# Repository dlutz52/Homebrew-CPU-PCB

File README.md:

# Homebrew CPU Project PCB

My inspiration for this PCB came from following Ian Ward's project on his web site:

[20xt6 Homebrew CPU Project](https://excess.org/cpu/)

This PCB implements the [LCD Character Display: Milestone 1 Complete!](https://www.youtube.com/watch?v=neW9uogt1gw) stage of this series of videos. 

But there is more to come in the future, so checkout Ian's videos on his future plans:

[Discrete Logic Rhythm Game Prototype (no CPU)](https://www.youtube.com/watch?v=yo5xX4GLc_U)

[Designing a Rhythm Game: Homebrew CPU Plan Step 2](https://www.youtube.com/watch?v=taPa7SQpib4)

[Maze Game Prototype (no CPU!)](https://www.youtube.com/shorts/fGyHHWiAYDM)

I will try to keep up with him.

PCB Front Image

PCB Back Image

# Homebrew CPU PCB BOM

## Wed, Mar 21, 2024, 08:58:15

## Component Count: 25

Ref | Qty | Value | Vendor\Part # | Description
----|-----|-------|---------------|-----------
C1, C3, C5 | 3 | 10uF | Generic | Electrolytic capacitor
C2, C4, C6 | 2 | .01uF | Digikey\FG28C0G1H103JNT06 | Unpolarized capacitor 
D1 | 1 | YELLOW\Reset | Generic | LED\3mm\Yellow
D2 | 1 | RED\HALT | Generic | LED\3mm\Red 
D3 | 1 | BLUE\CLOCK | Generic | LED\3mm\Blue
D4, D5 | 2 | 10_SEG_LED BAR_GRAPH (Blue) | Digikey\1497-1079-5-ND | LED Bar Graph\Blue\1x10 
D6 | 1 | 10_SEG_LED  BAR_GRAPH (Yellow) | Digikey\754-1179-5-ND | LED Bar Graph\Yellow\1x10 
D7 | 1 | GREEN | Generic | LED\3mm\Green 
J1 | 1 | PinSocket_1x16_P2.54mm_Vertical | Generic | Female Pin Header\1x16\2.54mm pitch
J2 | 1 | UJC-HP-M-G-5-MSMT-TR | Digikey\2223-UJC-HP-M-G-5-MSMT-TRDKR-ND | Type C/20 VDC/3A/Horizontal/6 Pin/Power Only
R1, R3, R8 | 3 | 1Kohm | Digikey\13-MFR-25FTE52-1KCT-ND | Resistor\1Kohm\1%\1/4W\Axial
R2, R6, R7, R9 | 4 | 330ohm | Digikey\13-MFR-25FRF52-330RCT-ND | Resistor\330ohm\1%\1/4W\Axial
R4 | 1 | 220ohm | Generic | Resistor\220ohm\1%\1/4W\Axial
R5 | 1 | 3ohm | Generic | Resistor\3ohm\1%\1/4W\Axial
R10, R11 | 2 | 5.1Kohm | Digikey\13-MFR-25FTE52-5K1CT-ND | Resistor\5K1ohm\1%\1/4W\Axial
RN1, RN2, RN3 | 3 | 470ohm | Digikey\4609X-101-471LF-ND | Resistor Array\8 Resistors\470ohm\9SIP
RV1 | 1 | 10Kohm | Jameco\2276439 | Panasonic EWAQ30C15A14 Audio Slide Pot
RV2, RV3 | 2 | 5Kohm | Digikey\3386P-1-502LF | Trimmer Pot\5Kohms\0.5W\1/2W\Through Hole
SW1 | 1 | TL2230 | Digikey\EG6031-ND | Switch\Pushbutton\DPDT\Through Hole
S1 | 1 | REG SELECT | Digikey\450-1654-ND | Switch\Tactile\SPST-NO\0.05A\24V\Through Hole
S2 | 1 | ENABLE | Digikey\450-1654-ND | Switch\Tactile\SPST-NO\0.05A\24V\Through Hole
U1, U3 | 2 | LM555 | Digikey\LM555CNNS/NOPB-ND | 555 Timer/Oscillator\100kHz\8-PDIP
U2 | 1 | 74LS00 | Digikey\296-1626-ND | NAND Gate IC 4 Channel 14-PDIP
U4, U5, U6, U7, U8 | 5 | 74LS163 | Digikey\296-3661-5-ND | Binary Counter\4 Bit\Positive Edge\16-PDIP
U9, U10 | 2 | SST39SF040-70-4C-PHE | Digikey\SST39SF040-70-4C-PHE-ND | FLASH Memory\4Mbit\70ns\32-PDIP

The LCD and its 16-pin male header are represented only with 3D models, but you need a 2004 LCD with a soldered 16-pin male header with a pitch of 2.54mm to plug into the 16 pin female header to complete this PCB. I have found the best place to get these is on eBay.

Do NOT try to use a 2004 LCD with an I<sup>2</sup>C adapter on it.

Most symbols/footprints/models are contained under the 'libraries' directory. Capacitors, resistors and LEDs use KiCad symbols/footprints/models.

KiCad 7.0.10 was used to create this PCB. KiCad 8.0.1 is out now and this project opens in that version. The newer KiCad will warn that this project was created in previous version and will be saved in a the newer format. When closing the schematic or a PCB just discard any changes. If you do not you will not be able to use KiCad 7 any more without difficulties.

Models in KiCad's 3D view will display an appropriate socket under the ICs but these can be omitted on the PCB - they are used to make it easier to replace any components should they need it in the future. The only exceptions are the sockets for the SST39SF040 FLASH chips. These chips can be changed out for different program\lookup combinations, so you do not want to solder them to the PCB. I would recommend using 32-pin sockets from Aries Electronics or something equivalent, for example, Digikey\A410AE-ND.

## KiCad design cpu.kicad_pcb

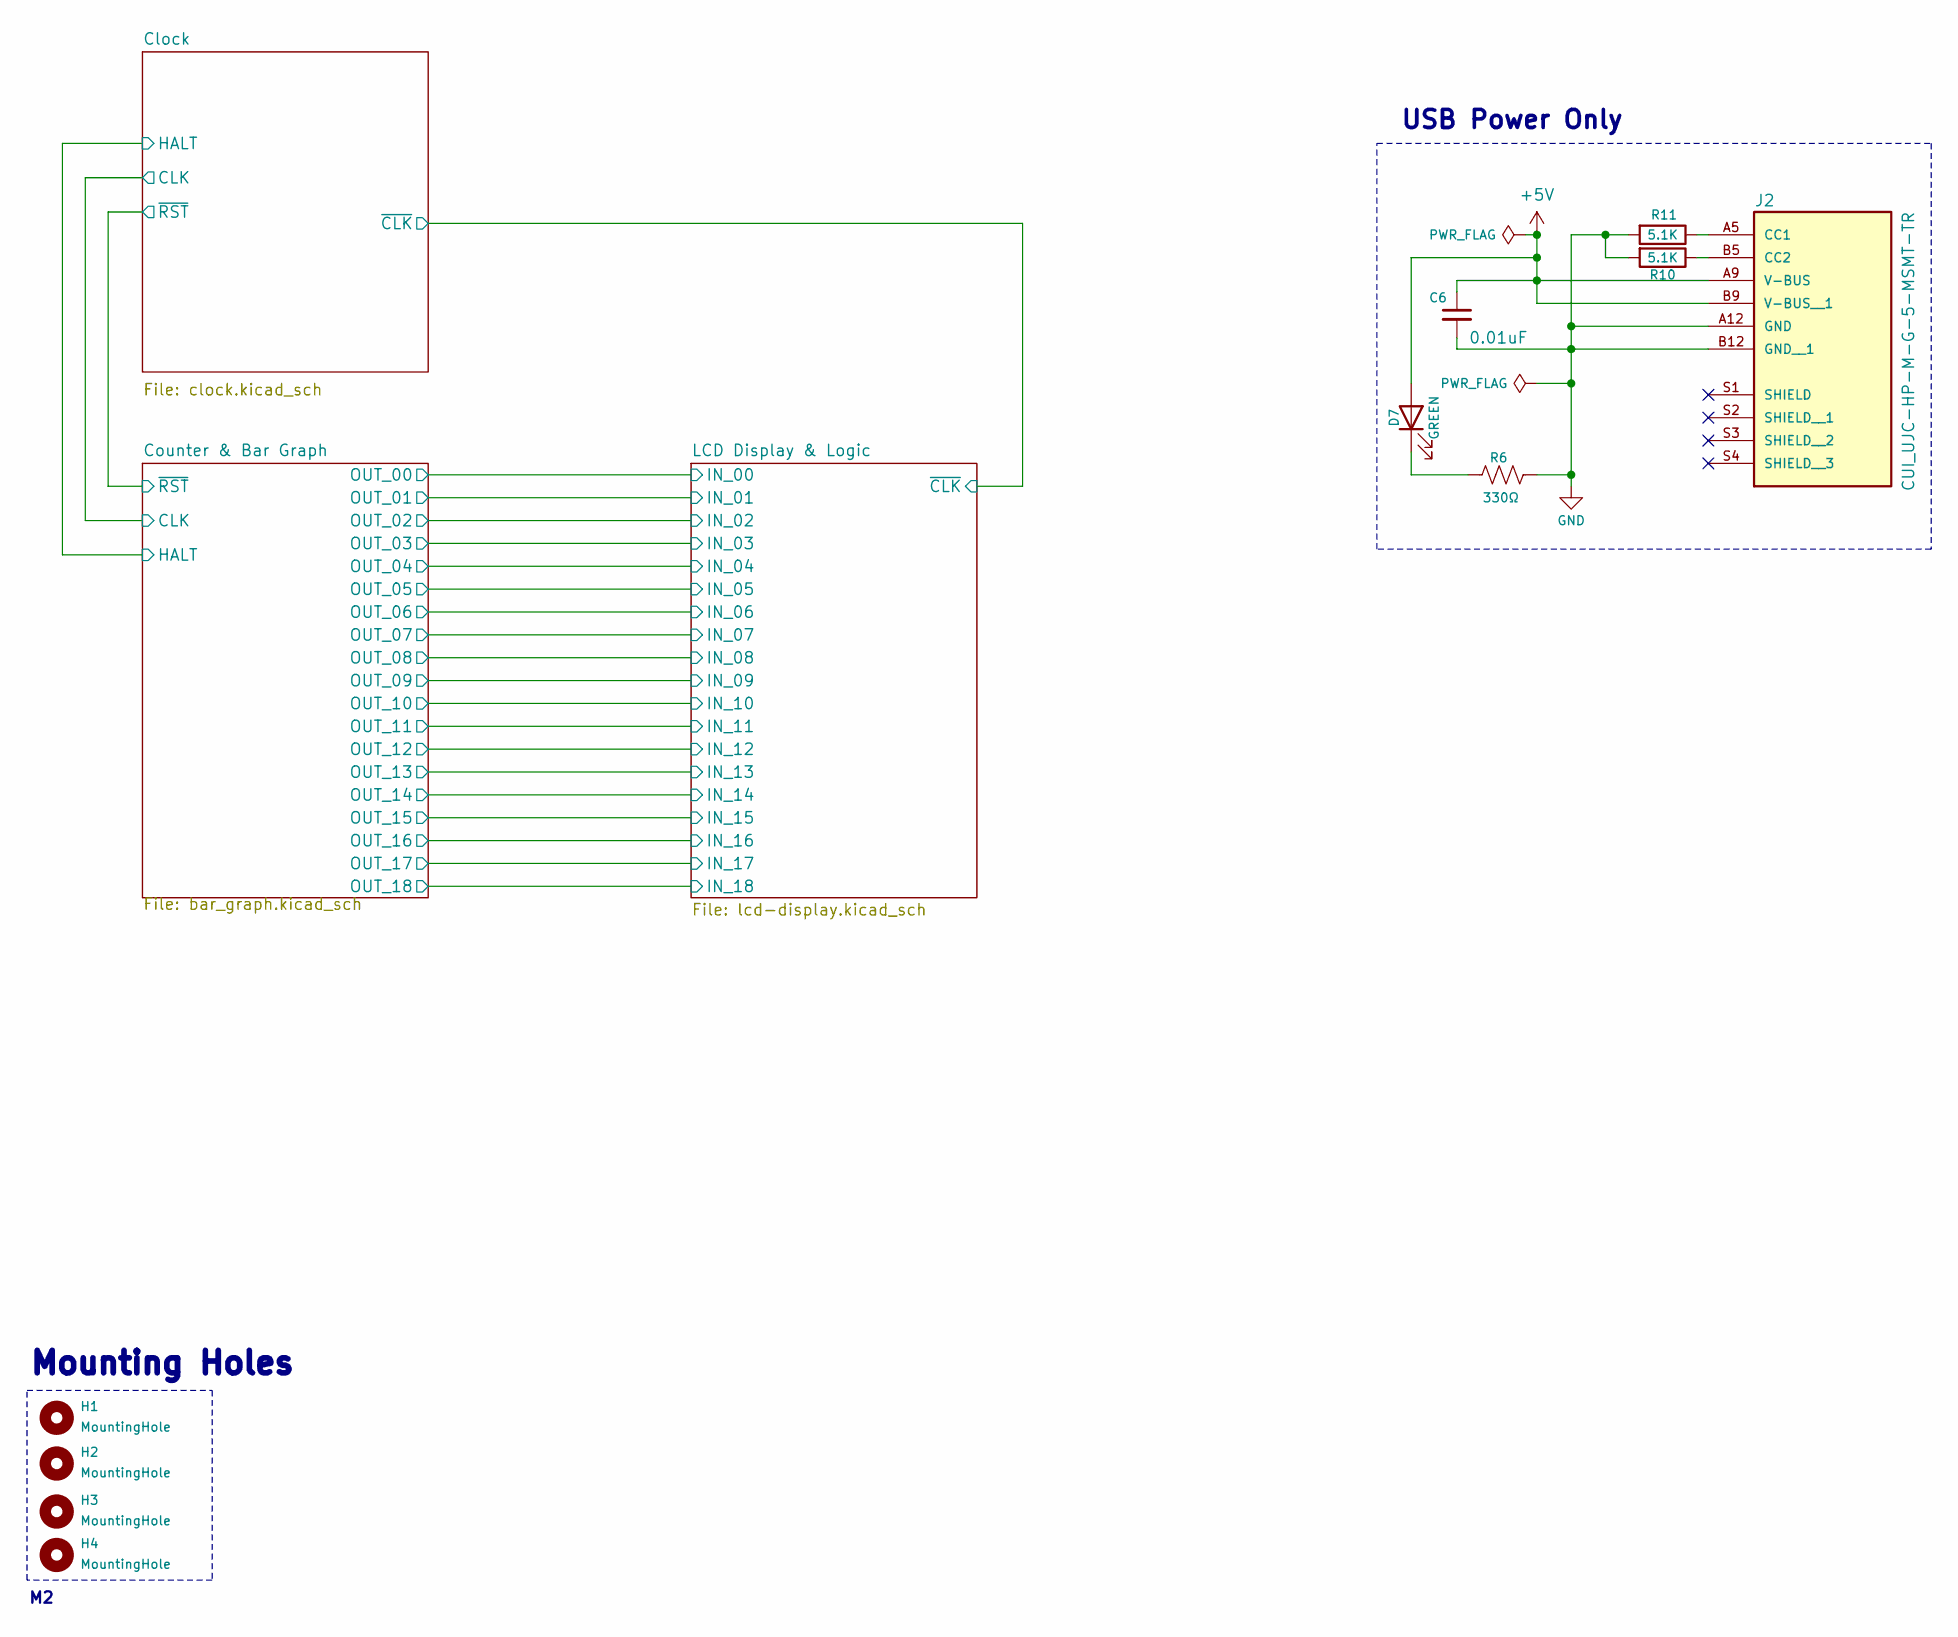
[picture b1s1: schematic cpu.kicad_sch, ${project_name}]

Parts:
C6: 0.01uF; C_Disc_D4.7mm_W2.5mm_P5.00mm
D7: GREEN; LED_D3.0mm
H1, H2, H3, H4: MountingHole; MountingHole_2.7mm_M2.5
J2: CUI_UJC-HP-M-G-5-MSMT-TR; PARTREV 04/30/2020
R6: 330Ω; R_Axial_DIN0207_L6.3mm_D2.5mm_P7.62mm_Horizontal
R10, R11: 5.1K; R_Axial_DIN0207_L6.3mm_D2.5mm_P7.62mm_Horizontal

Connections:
+5V: C6.1, D7.2 (A), J2.A9 (V-BUS), J2.B9 (V-BUS__1); also elsewhere on the board
GND: C6.2, J2.A12 (GND), J2.B12 (GND__1), R6.1, R10.2, R11.2; also elsewhere on the board
unnamed: D7.1 (K), R6.2
unnamed: J2.A5 (CC1), R11.1
unnamed: J2.B5 (CC2), R10.1

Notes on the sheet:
Mounting Holes
USB Power Only

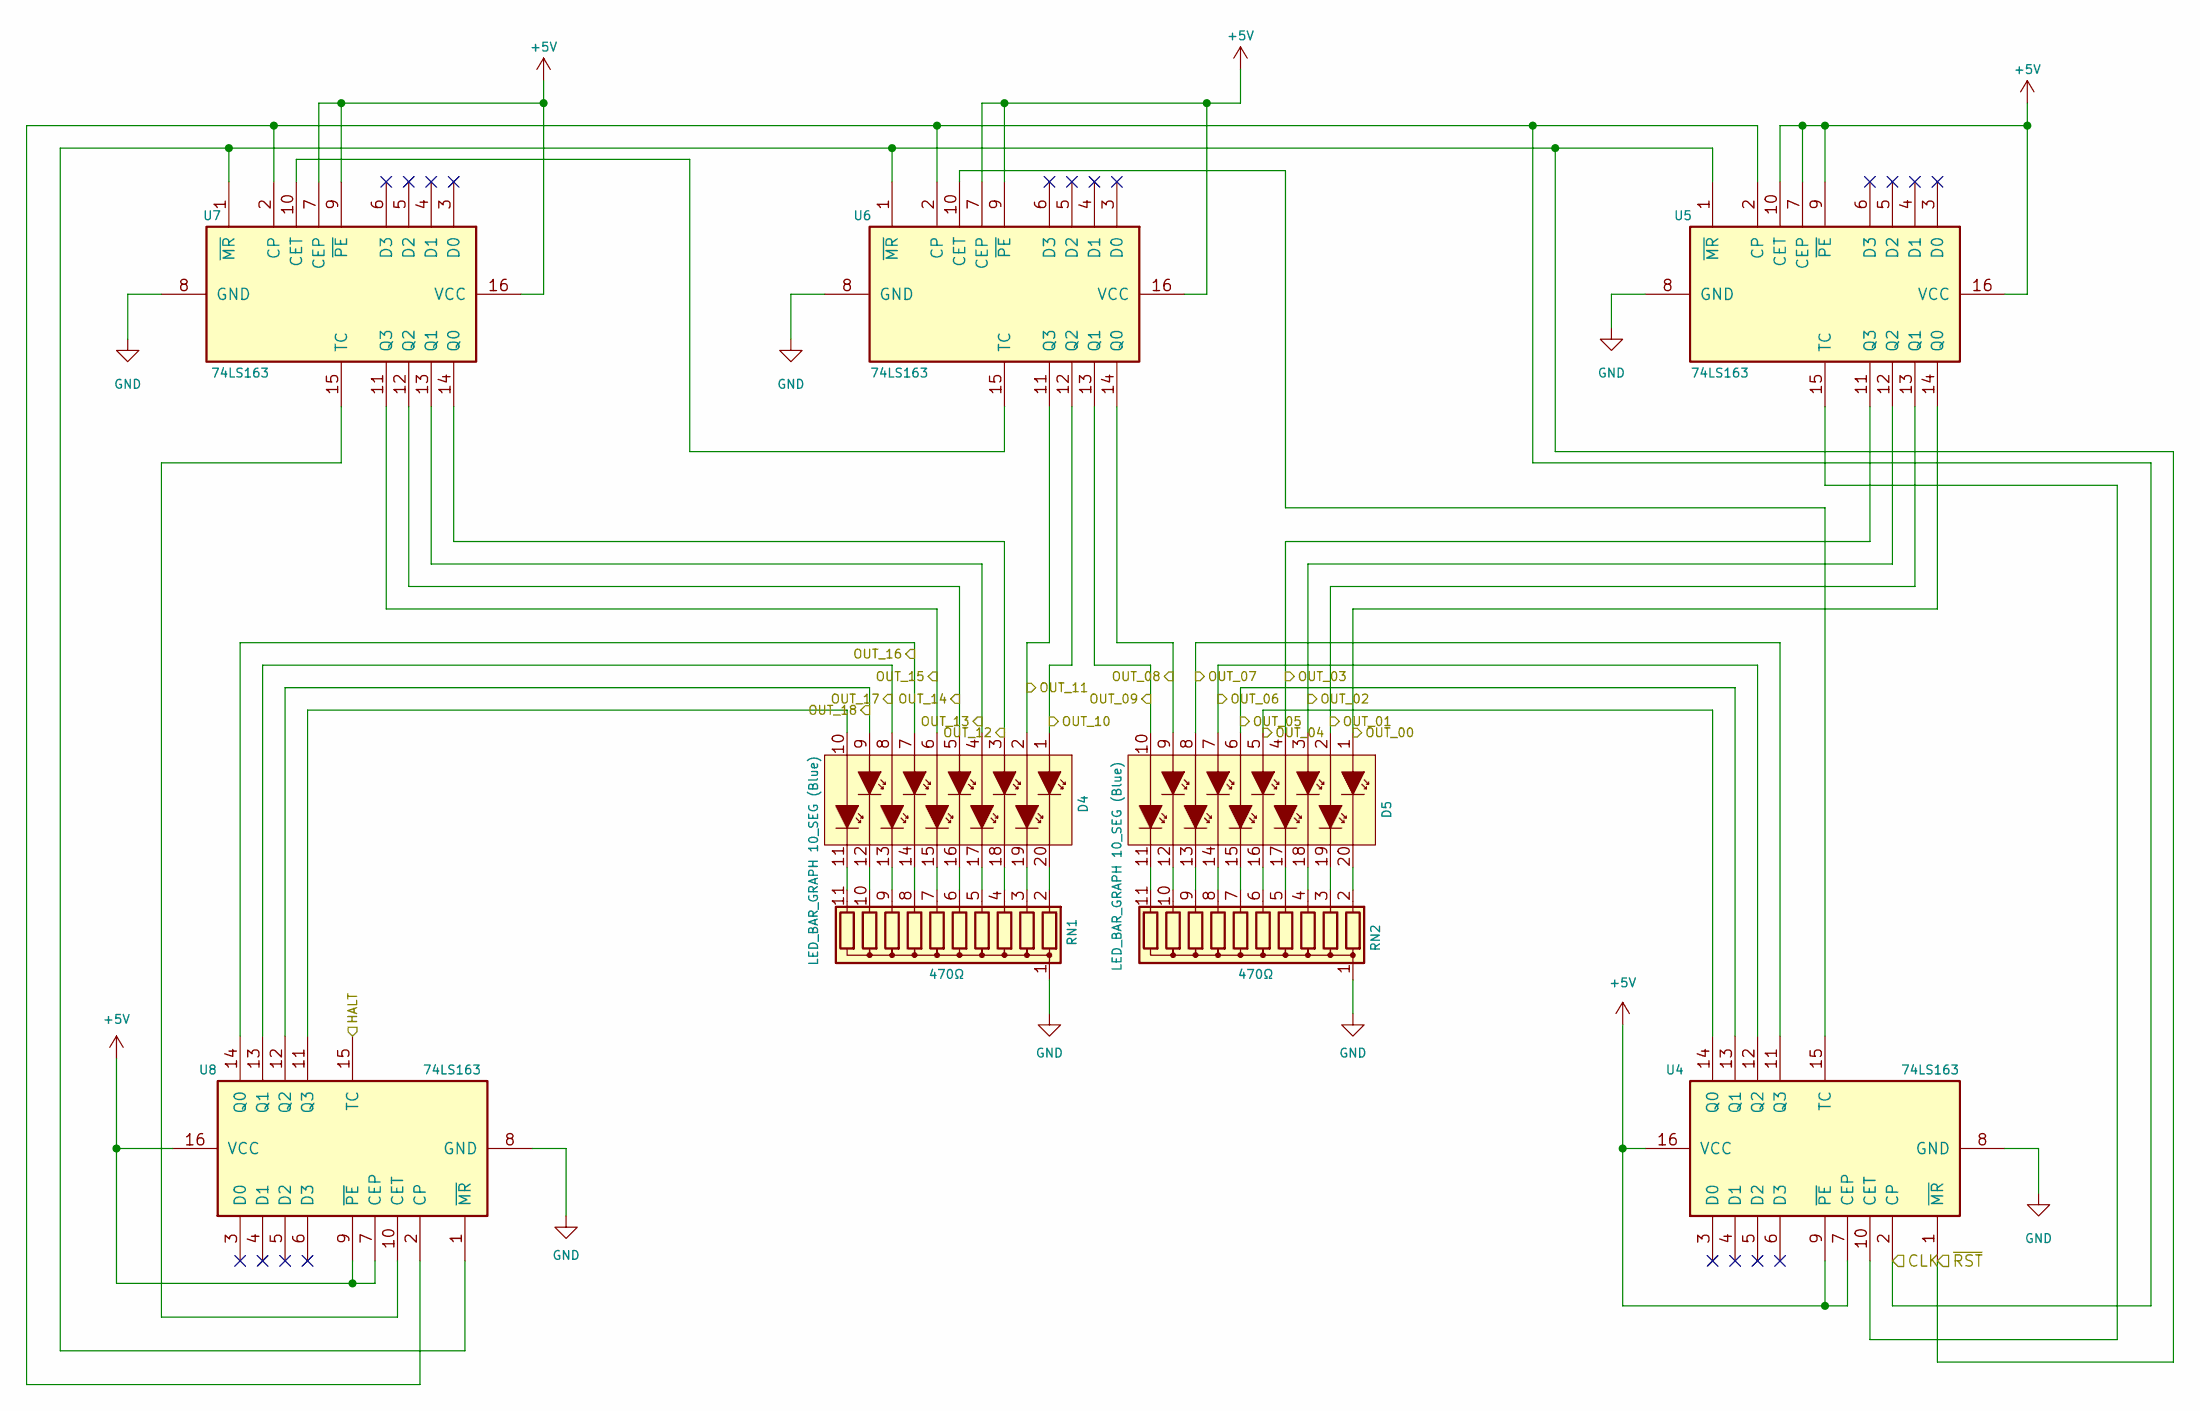
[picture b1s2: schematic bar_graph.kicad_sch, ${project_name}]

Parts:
D4, D5: LED_BAR_GRAPH 10_SEG (Blue); LED_Bar_Graph_10_SEG
RN1, RN2: 470Ω; R_Array_SIP11
U4, U5, U6, U7, U8: 74LS163; DIP-16_W7.62mm_Socket

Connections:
+5V: U4.7 (CEP), U4.9 (~PE), U4.16 (VCC), U5.7 (CEP), U5.9 (~PE), U5.10 (CET), U5.16 (VCC), U6.7 (CEP), U6.9 (~PE), U6.16 (VCC), U7.7 (CEP), U7.9 (~PE), U7.16 (VCC), U8.7 (CEP), U8.9 (~PE), U8.16 (VCC); also elsewhere on the board
/Clock/CLK: U4.2 (CP), U5.2 (CP), U6.2 (CP), U7.2 (CP), U8.2 (CP); also elsewhere on the board
/Clock/HALT: U8.15 (TC); also elsewhere on the board
/Clock/~RST: U4.1 (~MR), U5.1 (~MR), U6.1 (~MR), U7.1 (~MR), U8.1 (~MR); also elsewhere on the board
/Counter & Bar Graph/OUT_00: D5.1, U5.14 (Q0); also elsewhere on the board
/Counter & Bar Graph/OUT_01: D5.2, U5.13 (Q1); also elsewhere on the board
/Counter & Bar Graph/OUT_02: D5.3, U5.12 (Q2); also elsewhere on the board
/Counter & Bar Graph/OUT_03: D5.4, U5.11 (Q3); also elsewhere on the board
/Counter & Bar Graph/OUT_04: D5.5, U4.14 (Q0); also elsewhere on the board
/Counter & Bar Graph/OUT_05: D5.6, U4.13 (Q1); also elsewhere on the board
/Counter & Bar Graph/OUT_06: D5.7, U4.12 (Q2); also elsewhere on the board
/Counter & Bar Graph/OUT_07: D5.8, U4.11 (Q3); also elsewhere on the board
/Counter & Bar Graph/OUT_08: D5.9, U6.14 (Q0); also elsewhere on the board
/Counter & Bar Graph/OUT_09: D5.10, U6.13 (Q1); also elsewhere on the board
/Counter & Bar Graph/OUT_10: D4.1, U6.12 (Q2); also elsewhere on the board
/Counter & Bar Graph/OUT_11: D4.2, U6.11 (Q3); also elsewhere on the board
/Counter & Bar Graph/OUT_12: D4.3, U7.14 (Q0); also elsewhere on the board
/Counter & Bar Graph/OUT_13: D4.4, U7.13 (Q1); also elsewhere on the board
/Counter & Bar Graph/OUT_14: D4.5, U7.12 (Q2); also elsewhere on the board
/Counter & Bar Graph/OUT_15: D4.6, U7.11 (Q3); also elsewhere on the board
/Counter & Bar Graph/OUT_16: D4.7, U8.14 (Q0); also elsewhere on the board
/Counter & Bar Graph/OUT_17: D4.8, U8.13 (Q1); also elsewhere on the board
/Counter & Bar Graph/OUT_18: D4.9, U8.12 (Q2); also elsewhere on the board
GND: RN1.1 (common), RN2.1 (common), U4.8 (GND), U5.8 (GND), U6.8 (GND), U7.8 (GND), U8.8 (GND); also elsewhere on the board
unnamed: D4.20, RN1.2 (R1)
unnamed: D4.19, RN1.3 (R2)
unnamed: D4.18, RN1.4 (R3)
unnamed: D4.17, RN1.5 (R4)
unnamed: D4.16, RN1.6 (R5)
unnamed: D4.15, RN1.7 (R6)
unnamed: D4.14, RN1.8 (R7)
unnamed: D4.13, RN1.9 (R8)
unnamed: D4.12, RN1.10 (R9)
unnamed: D4.11, RN1.11 (R10)
unnamed: D5.20, RN2.2 (R1)
unnamed: D5.19, RN2.3 (R2)
unnamed: D5.18, RN2.4 (R3)
unnamed: D5.17, RN2.5 (R4)
unnamed: D5.16, RN2.6 (R5)
unnamed: D5.15, RN2.7 (R6)
unnamed: D5.14, RN2.8 (R7)
unnamed: D5.13, RN2.9 (R8)
unnamed: D5.12, RN2.10 (R9)
unnamed: D5.11, RN2.11 (R10)
unnamed: U4.10 (CET), U5.15 (TC)
unnamed: U4.15 (TC), U6.10 (CET)
unnamed: U6.15 (TC), U7.10 (CET)
unnamed: U7.15 (TC), U8.10 (CET)
unnamed: D4.10, U8.11 (Q3)

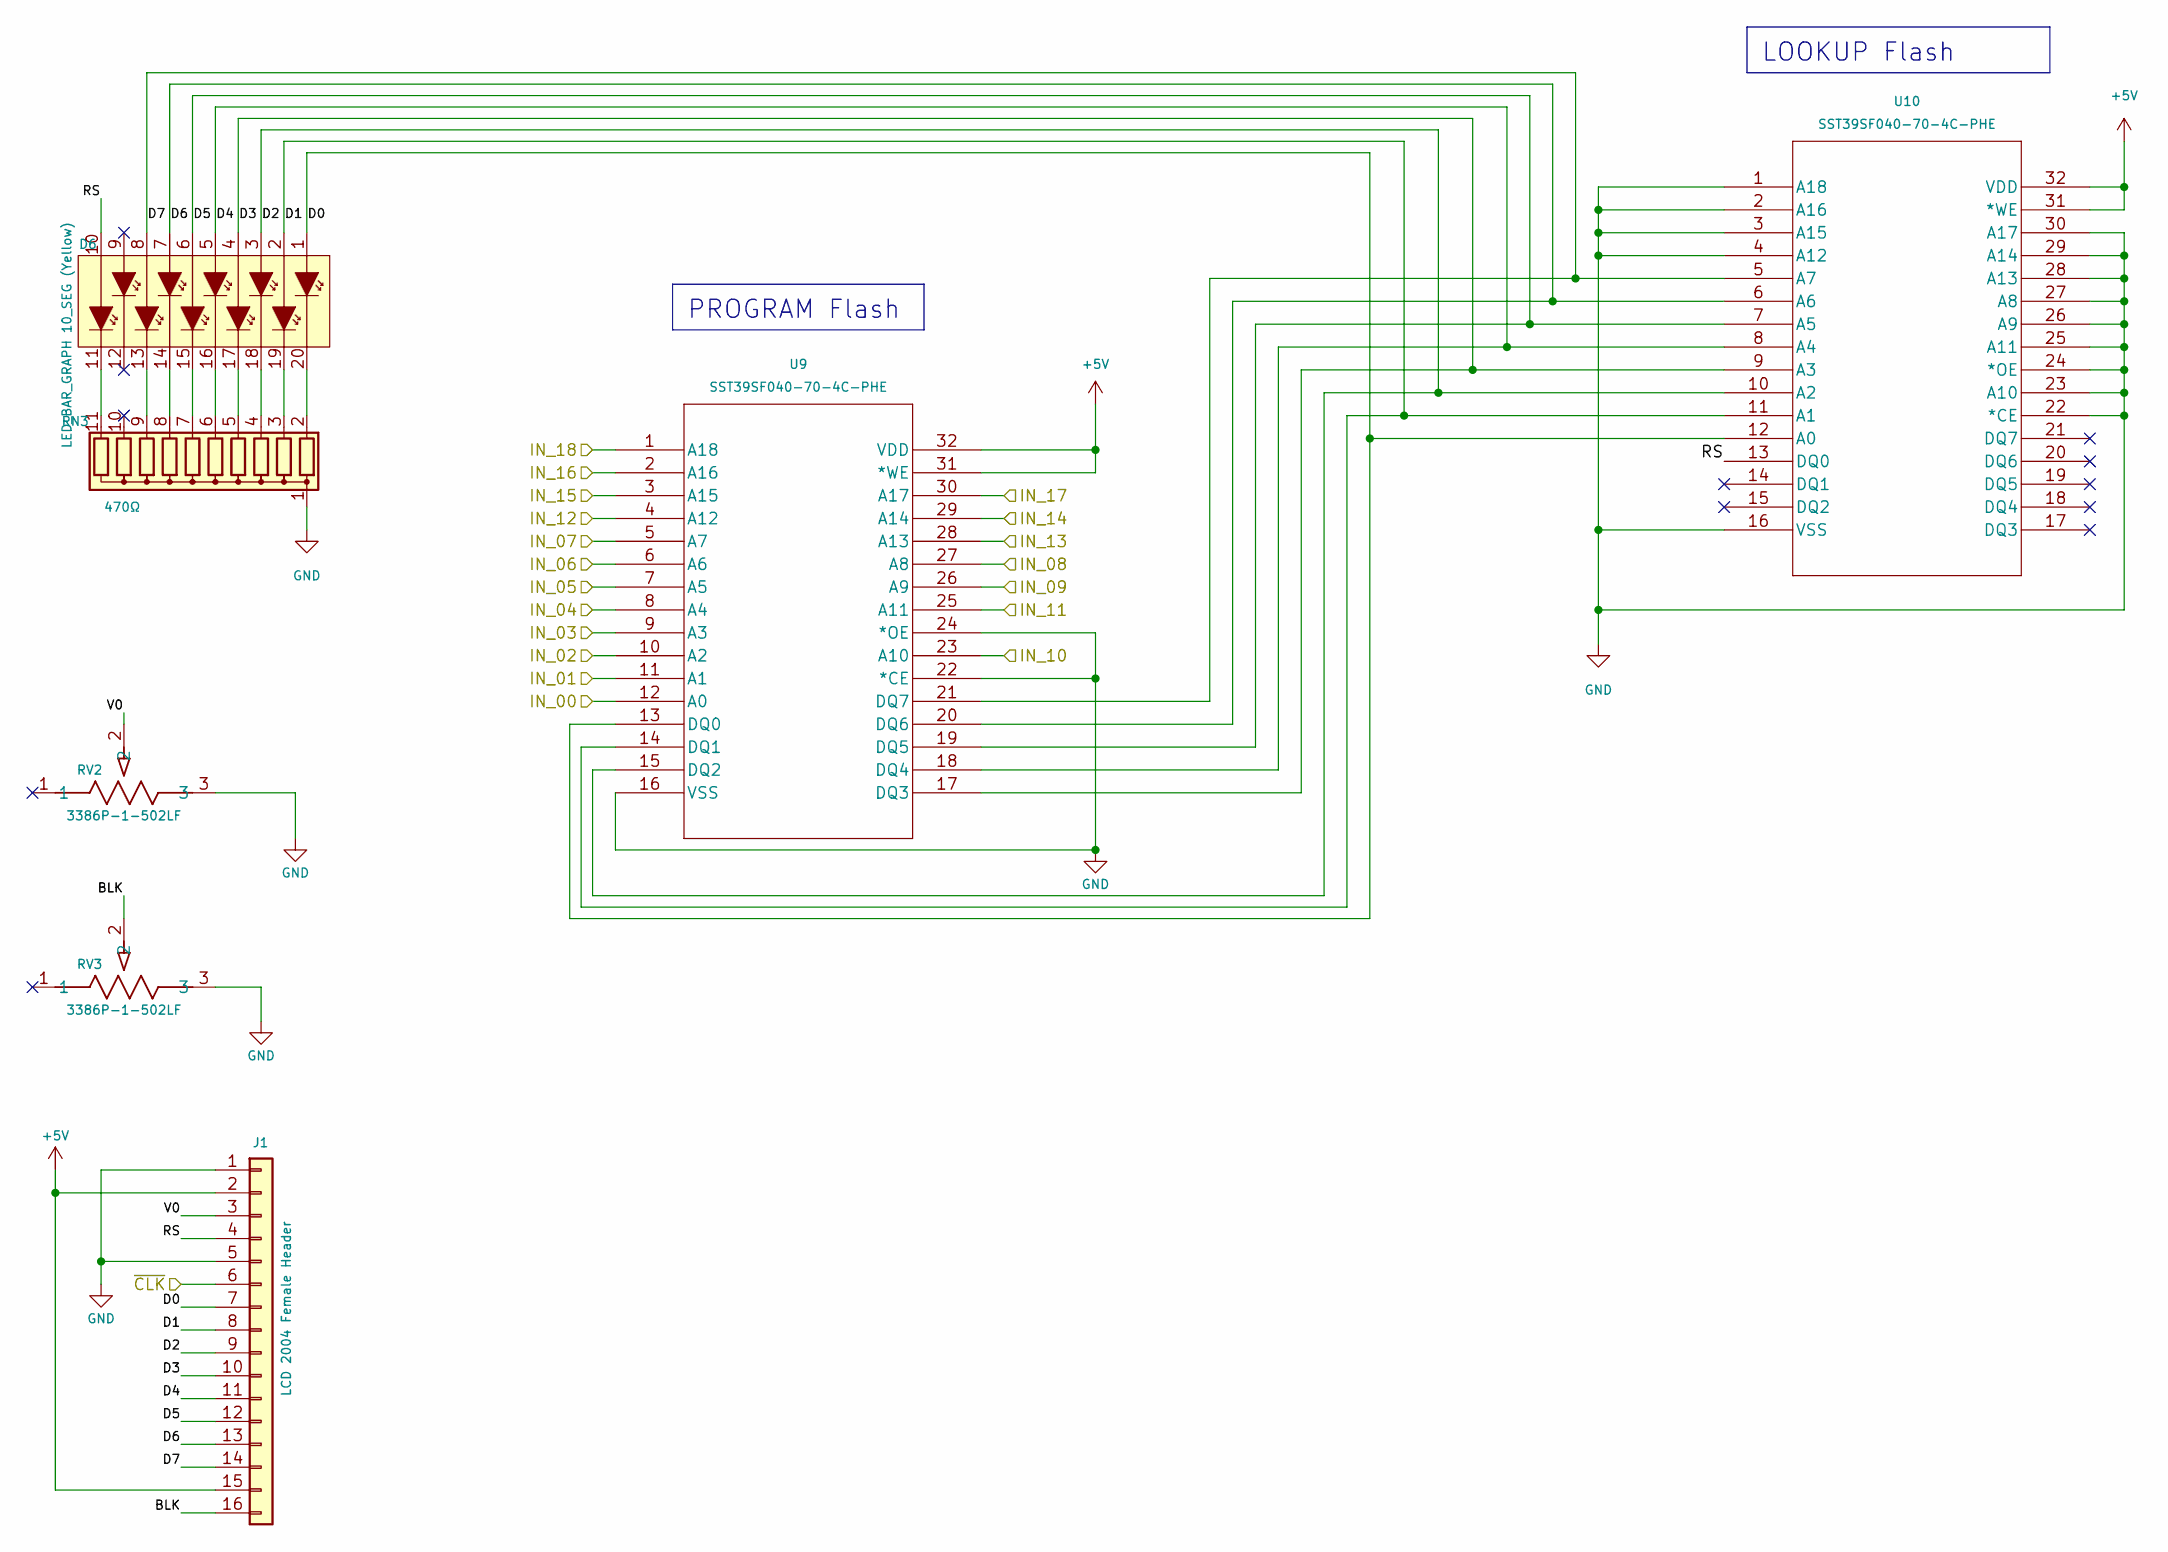
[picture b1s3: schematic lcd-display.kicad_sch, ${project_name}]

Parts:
D6: LED_BAR_GRAPH 10_SEG (Yellow); LED_Bar_Graph_10_SEG
J1: LCD 2004 Female Header; LCD_2004_PinSocket_1x16_P2.54mm_Vertical
RN3: 470Ω; R_Array_SIP11
RV2, RV3: 3386P-1-502LF; BOURNE-3386P; Digikey PN 3386P-502LF-ND
U9, U10: SST39SF040-70-4C-PHE; PDIP32_PH_SST_MCH

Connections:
+5V: J1.2, J1.15, U9.31 (*WE), U9.32 (VDD), U10.31 (*WE), U10.32 (VDD); also elsewhere on the board
/Clock/~CLK: J1.6; also elsewhere on the board
/Counter & Bar Graph/OUT_00: U9.12 (A0); also elsewhere on the board
/Counter & Bar Graph/OUT_01: U9.11 (A1); also elsewhere on the board
/Counter & Bar Graph/OUT_02: U9.10 (A2); also elsewhere on the board
/Counter & Bar Graph/OUT_03: U9.9 (A3); also elsewhere on the board
/Counter & Bar Graph/OUT_04: U9.8 (A4); also elsewhere on the board
/Counter & Bar Graph/OUT_05: U9.7 (A5); also elsewhere on the board
/Counter & Bar Graph/OUT_06: U9.6 (A6); also elsewhere on the board
/Counter & Bar Graph/OUT_07: U9.5 (A7); also elsewhere on the board
/Counter & Bar Graph/OUT_08: U9.27 (A8); also elsewhere on the board
/Counter & Bar Graph/OUT_09: U9.26 (A9); also elsewhere on the board
/Counter & Bar Graph/OUT_10: U9.23 (A10); also elsewhere on the board
/Counter & Bar Graph/OUT_11: U9.25 (A11); also elsewhere on the board
/Counter & Bar Graph/OUT_12: U9.4 (A12); also elsewhere on the board
/Counter & Bar Graph/OUT_13: U9.28 (A13); also elsewhere on the board
/Counter & Bar Graph/OUT_14: U9.29 (A14); also elsewhere on the board
/Counter & Bar Graph/OUT_15: U9.3 (A15); also elsewhere on the board
/Counter & Bar Graph/OUT_16: U9.2 (A16); also elsewhere on the board
/Counter & Bar Graph/OUT_17: U9.30 (A17); also elsewhere on the board
/Counter & Bar Graph/OUT_18: U9.1 (A18); also elsewhere on the board
/LCD Display & Logic/BLK: J1.16, RV3.2
/LCD Display & Logic/D0: D6.1, J1.7, U9.13 (DQ0), U10.12 (A0)
/LCD Display & Logic/D1: D6.2, J1.8, U9.14 (DQ1), U10.11 (A1)
/LCD Display & Logic/D2: D6.3, J1.9, U9.15 (DQ2), U10.10 (A2)
/LCD Display & Logic/D3: D6.4, J1.10, U9.17 (DQ3), U10.9 (A3)
/LCD Display & Logic/D4: D6.5, J1.11, U9.18 (DQ4), U10.8 (A4)
/LCD Display & Logic/D5: D6.6, J1.12, U9.19 (DQ5), U10.7 (A5)
/LCD Display & Logic/D6: D6.7, J1.13, U9.20 (DQ6), U10.6 (A6)
/LCD Display & Logic/D7: D6.8, J1.14, U9.21 (DQ7), U10.5 (A7)
/LCD Display & Logic/RS: D6.10, J1.4, U10.13 (DQ0)
/LCD Display & Logic/V0: J1.3, RV2.2
GND: J1.1, J1.5, RN3.1 (common), RV2.3, RV3.3, U9.16 (VSS), U9.22 (*CE), U9.24 (*OE), U10.1 (A18), U10.2 (A16), U10.3 (A15), U10.4 (A12), U10.16 (VSS), U10.22 (*CE), U10.23 (A10), U10.24 (*OE), U10.25 (A11), U10.26 (A9), U10.27 (A8), U10.28 (A13), U10.29 (A14), U10.30 (A17); also elsewhere on the board
unnamed: D6.20, RN3.2 (R1)
unnamed: D6.19, RN3.3 (R2)
unnamed: D6.18, RN3.4 (R3)
unnamed: D6.17, RN3.5 (R4)
unnamed: D6.16, RN3.6 (R5)
unnamed: D6.15, RN3.7 (R6)
unnamed: D6.14, RN3.8 (R7)
unnamed: D6.13, RN3.9 (R8)
unnamed: D6.11, RN3.11 (R10)

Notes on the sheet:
LOOKUP Flash
PROGRAM Flash

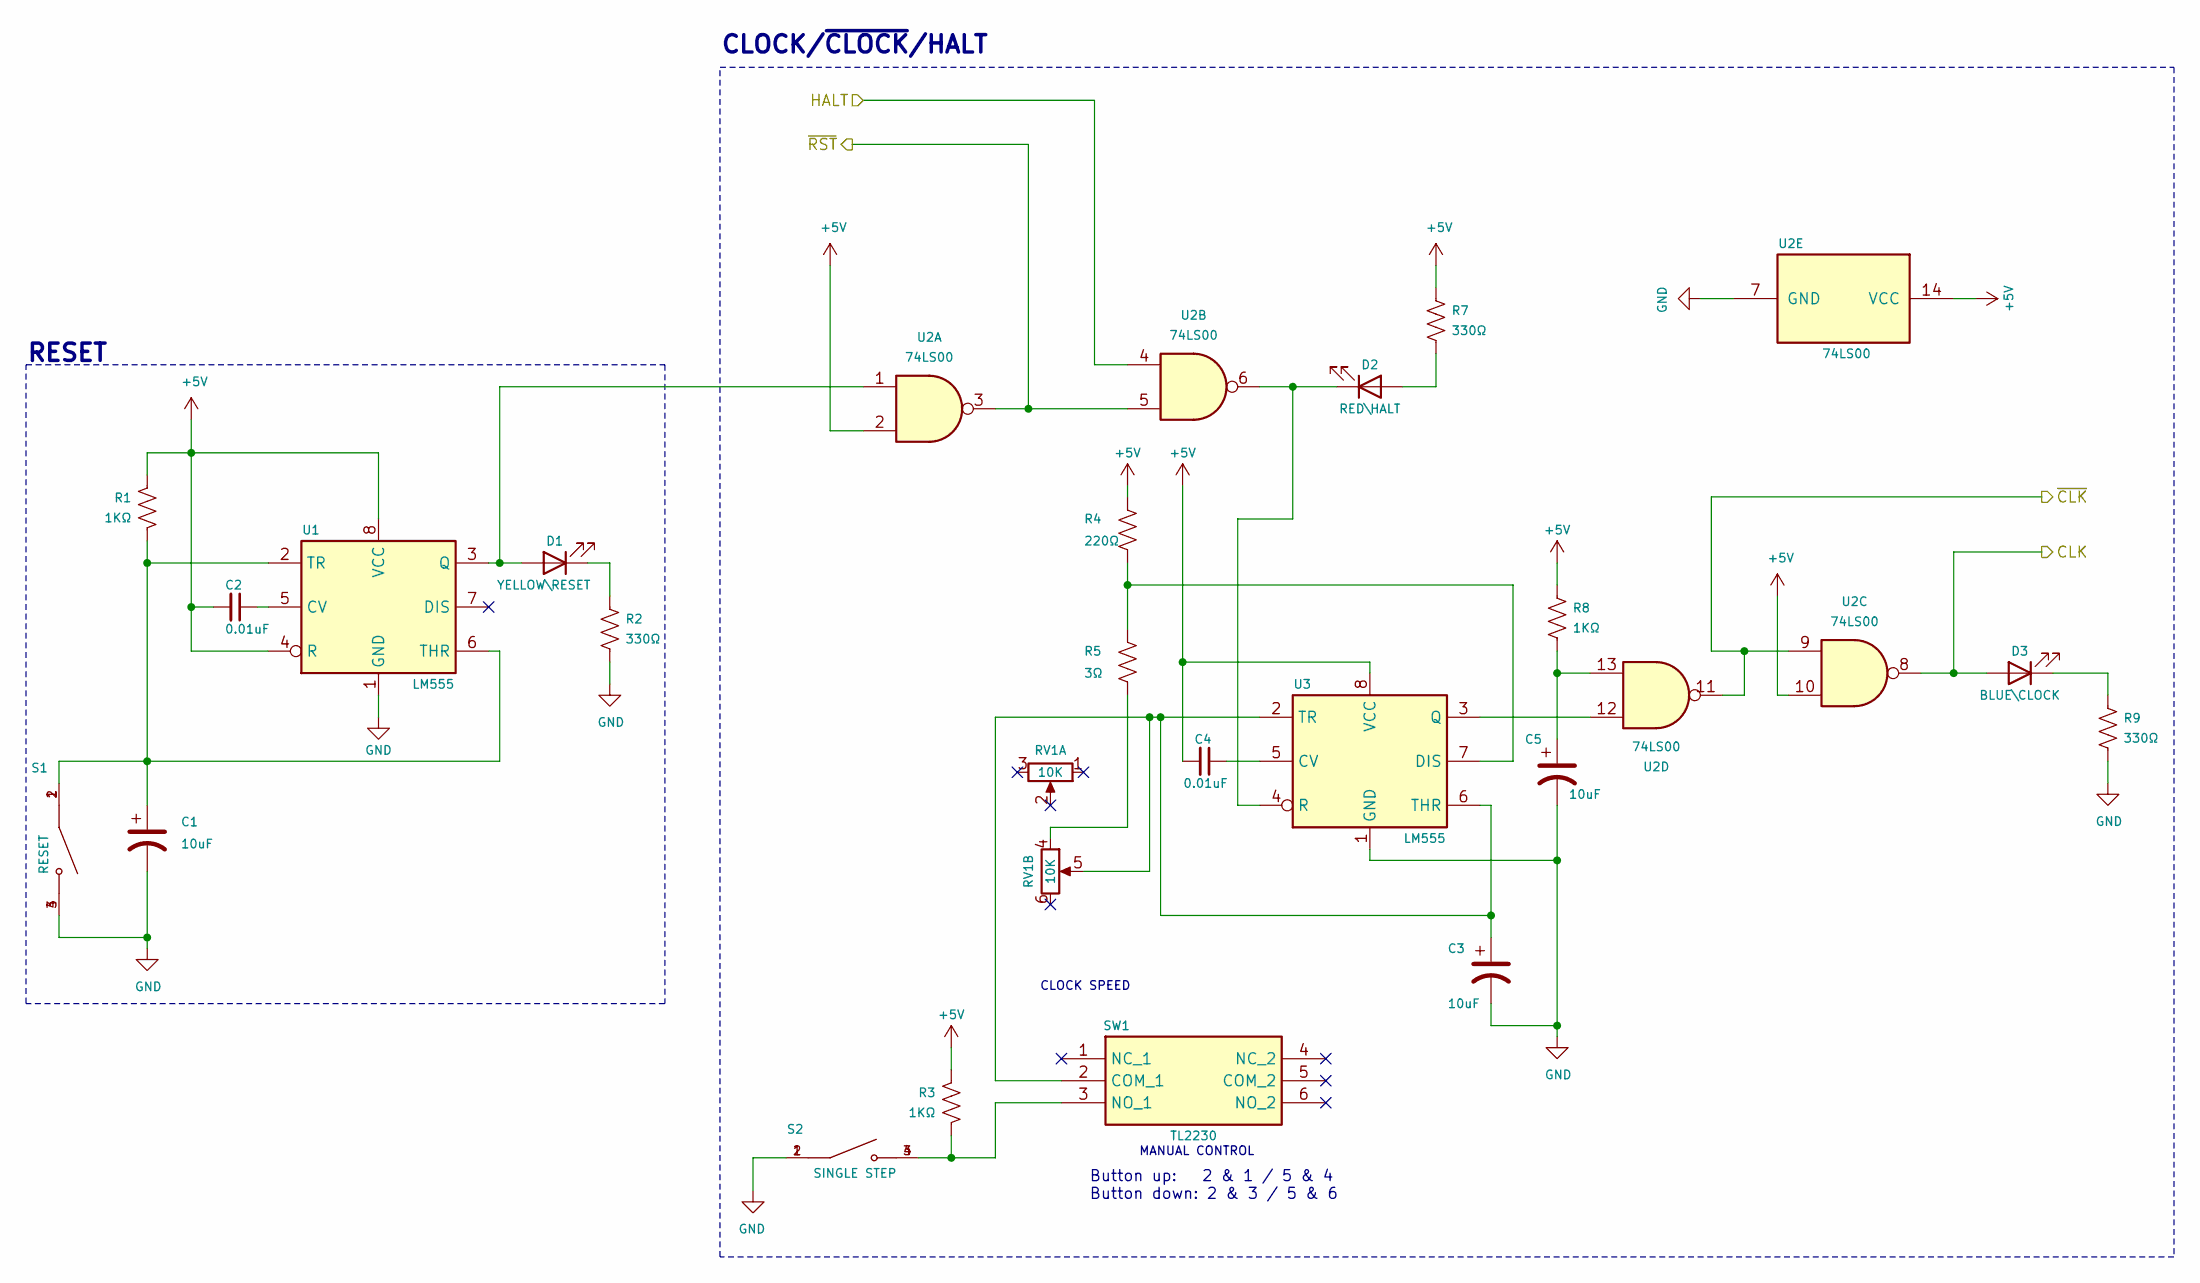
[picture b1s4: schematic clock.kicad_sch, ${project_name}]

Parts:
C1, C3, C5: 10uF; CP_Radial_D4.0mm_P2.00mm
C2, C4: 0.01uF; C_Disc_D4.7mm_W2.5mm_P5.00mm
D1: YELLOW\RESET; LED_D3.0mm
D2: RED\HALT; LED_D3.0mm
D3: BLUE\CLOCK; LED_D3.0mm
R1, R3, R8: 1KΩ; R_Axial_DIN0207_L6.3mm_D2.5mm_P7.62mm_Horizontal
R2, R7, R9: 330Ω; R_Axial_DIN0207_L6.3mm_D2.5mm_P7.62mm_Horizontal
R4: 220Ω; R_Axial_DIN0207_L6.3mm_D2.5mm_P7.62mm_Horizontal
R5: 3Ω; R_Axial_DIN0207_L6.3mm_D2.5mm_P7.62mm_Horizontal
RV1: 10K; 10K_Audio_Slide_Pot
S1: RESET; SW_1825967-1
S2: SINGLE STEP; SW_1825967-1
SW1: TL2230; TL2230EEF140; Mouser Part Number 612-TL2230EEF140
U1, U3: LM555; DIP-8_W7.62mm_Socket
U2: 74LS00; DIP-14_W7.62mm_Socket

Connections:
+5V: C2.2, C4.2, R1.1, R3.1, R4.1, R7.2, R8.1, U1.4 (R), U1.8 (VCC), U2.2, U2.10, U2.14 (VCC), U3.8 (VCC); also elsewhere on the board
/Clock/CLK: D3.2 (A), U2.8; also elsewhere on the board
/Clock/HALT: U2.4; also elsewhere on the board
/Clock/~CLK: U2.9, U2.11; also elsewhere on the board
/Clock/~RST: U2.3, U2.5; also elsewhere on the board
GND: C1.2, C3.2, C5.2, R2.1, R9.1, S1.3, S1.4, S2.1, S2.2, U1.1 (GND), U2.7 (GND), U3.1 (GND); also elsewhere on the board
unnamed: C5.1, R8.2, U2.13
unnamed: D1.2 (A), U1.3 (Q), U2.1
unnamed: D1.1 (K), R2.2
unnamed: D2.2 (A), R7.1
unnamed: D2.1 (K), U2.6, U3.4 (R)
unnamed: D3.1 (K), R9.2
unnamed: R5.2, RV1.4
unnamed: C3.1, RV1.5, SW1.2 (COM_1), U3.2 (TR), U3.6 (THR)
unnamed: R3.2, S2.3, S2.4, SW1.3 (NO_1)
unnamed: C2.1, U1.5 (CV)
unnamed: C1.1, R1.2, S1.1, S1.2, U1.2 (TR), U1.6 (THR)
unnamed: C4.1, U3.5 (CV)
unnamed: R4.2, R5.1, U3.7 (DIS)
unnamed: U2.12, U3.3 (Q)

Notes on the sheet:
Button up: 2 & 1 / 5 & 4 Button down: 2 & 3 / 5 & 6
CLOCK SPEED
RESET
CLOCK/~{CLOCK}/HALT
MANUAL CONTROL

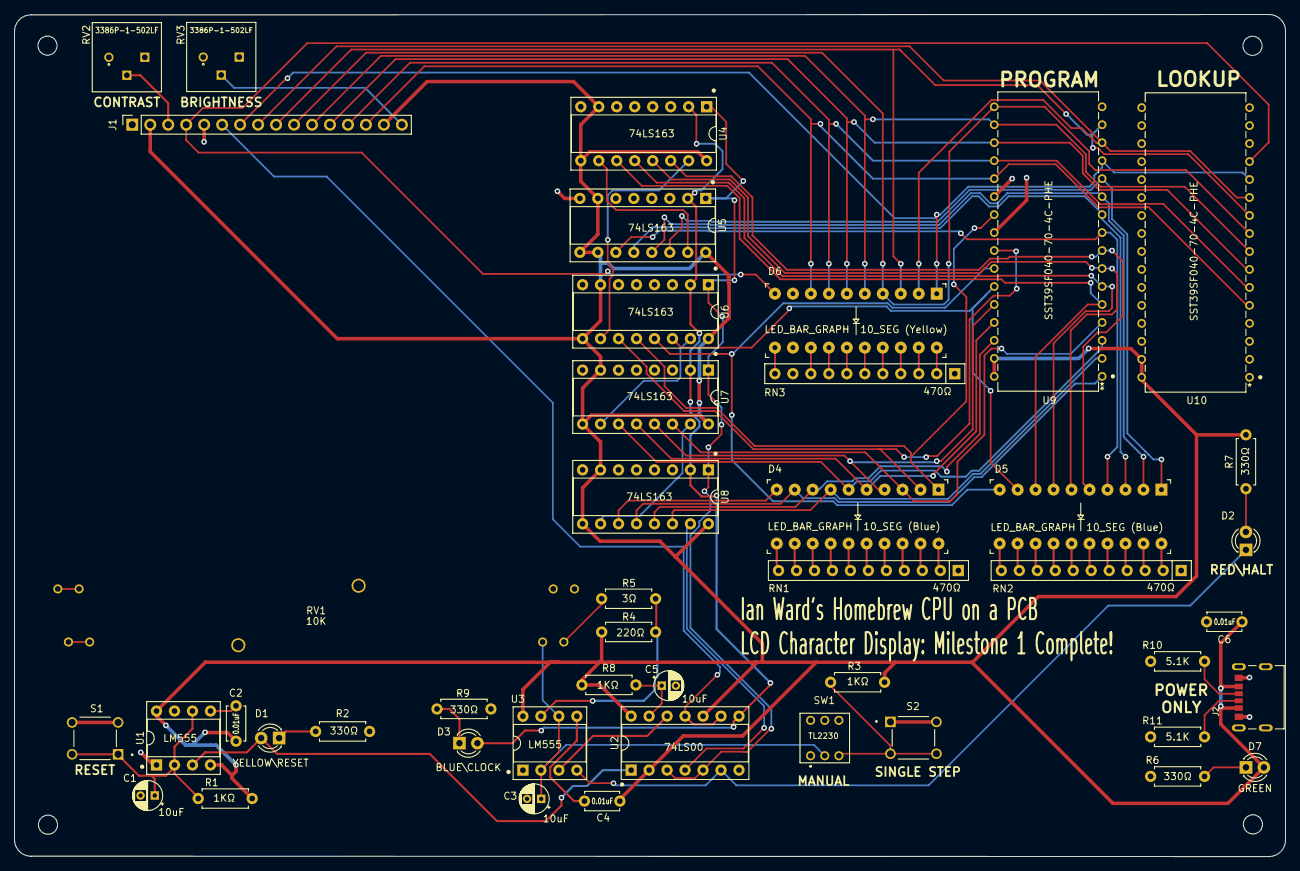
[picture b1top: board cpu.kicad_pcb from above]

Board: 2 copper layers, 179.6 x 119.0 mm, 49 parts (0 on the bottom side), 87 nets.

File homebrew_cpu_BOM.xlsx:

# | Reference | Qty | Value | Footprint | Vendor\Part # | Vendor URL | Datasheet | Description
1 | C1, C3, C5 | 3 | 10µF | Capacitor_THT:CP_Radial_D4.0mm_P2.00mm | Generic |  |  | Electrolytic capacitor
2 | C2, C4, C6 | 2 | 0.01µF | Capacitor_THT:C_Disc_D4.7mm_W2.5mm_P5.00mm | Digikey\445-173474-1-ND | https://www.digikey.com/en/products/detail/tdk-corporation/F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 | https://product.tdk.com/en/system/files?file=dam/doc/product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 | Unpolarized capacitor
3 | D1 | 1 | YELLOW\RESET | LED_THT:LED_D3.0mm | Generic |  |  | LED\3mm\Yellow
4 | D2 | 1 | RED\HALT | LED_THT:LED_D3.0mm | Generic |  |  | LED\3mm\Red
5 | D3 | 1 | BLUE\CLOCK | LED_THT:LED_D3.0mm | Generic |  |  | LED\3mm\Blue
6 | D4, D5 | 2 | LED_BAR_GRAPH 10_SEG | Homebrew-CPU-PCB:LED_Bar_Graph_10_SEG (Blue) | Digikey\1497-1079-5-ND | https://www.digikey.com/en/products/detail/sunled/XGCBDX10D/4745980 | https://www.sunledusa.com/products/spec/XGCBDX10D.pdf | LED Bar Graph\Blue\1x10
7 | D6 | 1 | LED_BAR_GRAPH 10_SEG | Homebrew-CPU-PCB:LED_Bar_Graph_10_SEG (Yellow) | Digikey\754-1179-5-ND | https://www.digikey.com/en/products/detail/kingbright/DC10YW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 | https://www.kingbrightusa.com/images/catalog/SPEC/DC10YWA.pdf | LED Bar Graph\Yellow\1x10
8 | D7 | 1 | GREEN\POWER | LED_THT:LED_D3.0mm | Generic |  |  | LED\3mm\Green
9 | J1 | 1 | LCD 2004 Female Header | Homebrew-CPU-PCB:LCD_2004_PinSocket_1x16_P2.54mm_Vertical | Generic |  |  | Female Pin Header\1x16\2.54mm pitch
10 | J2 | 1 | CUI_UJC-HP-M-G-5-MSMT-TR | Homebrew-CPU-PCB:CUI_UJC-HP-M-G-5-MSMT-TR | Digikey\2223-UJC-HP-M-G-5-MSMT-TRDKR-ND | https://www.digikey.com/en/products/detail/cui-devices/UJC-H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 | https://www.cuidevices.com/product/resource/ujc-hp-m-g-5-msm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 | Type C/20 VDC/3A/Horizontal/6 Pin/Power Only
11 | R1, R3, R8 | 3 | 1Kohm | Resistor_THT:R_Axial_DIN0207_L6.3mm_D2.5mm_P7.62mm_Horizontal | Digikey\13-MFR-25FTE52-1KCT-ND | https://www.digikey.com/en/products/detail/yageo/MFR-25FTE52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 | https://www.yageo.com/upload/media/product/app/datasheet/lr/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 | Resistor\1Kohm\1%\1/4W\Axial
12 | R2, R6, R7, R9 | 4 | 330ohm | Resistor_THT:R_Axial_DIN0207_L6.3mm_D2.5mm_P7.62mm_Horizontal | Digikey\13-MFR-25FRF52-330RCT-ND | https://www.digikey.com/en/products/detail/yageo/MFR-25FRF52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 | https://www.yageo.com/upload/media/product/app/datasheet/lr/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 | Resistor\330ohm\1%\1/4W\Axial
13 | R4 | 1 | 220ohm | Resistor_THT:R_Axial_DIN0207_L6.3mm_D2.5mm_P7.62mm_Horizontal | Generic |  |  | Resistor\220ohm\1%\1/4W\Axial
14 | R5 | 1 | 3ohm | Resistor_THT:R_Axial_DIN0207_L6.3mm_D2.5mm_P7.62mm_Horizontal | Generic |  |  | Resistor\3ohm\1%\1/4W\Axial
15 | R10, R11 | 2 | 5.1Kohm | Resistor_THT:R_Axial_DIN0207_L6.3mm_D2.5mm_P7.62mm_Horizontal | Digikey\13-MFR-25FTE52-5K1CT-ND | https://www.digikey.com/en/products/detail/yageo/MFR-25FTE52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 | https://www.yageo.com/upload/media/product/app/datasheet/lr/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 | Resistor\5K1ohm\1%\1/4W\Axial
16 | RN1, RN2, RN3 | 3 | 470ohm | Homebrew-CPU-PCB:R_Array_SIP11 | Digikey\4609X-101-471LF-ND | https://www.digikey.com/en/products/detail/bourns-inc/4609X-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 | https://www.bourns.com/docs/Product-Datasheets/4600x.pdf | Resistor Array\8 Resistors\470ohm\9SIP
17 | RV1 | 1 | 10Kohm | Homebrew-CPU-PCB:10K_Audio_Slide_Pot | Jameco\2276439 | https://www.jameco.com/webapp/wcs/stores/servlet/ProductDisp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 | https://www.jameco.com/Jameco/Products/ProdDS/2276439.pdf | Panasonic EWAQ30C15A14 Audio Slide Pot
18 | RV2, RV3 | 2 | 3386P-1-502LF | Homebrew-CPU-PCB:BOURNE-3386P | Digikey\3386P-1-502LF | https://www.digikey.com/en/products/detail/bourns-inc/3386P-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 | https://www.bourns.com/docs/Product-Datasheets/3386.pdf | Trimmer Pot\5Kohms\0.5W\1/2W\Through Hole
19 | S1 | 1 | RESET | Homebrew-CPU-PCB:SW_1825967-1 | Digikey\450-1654-ND | https://www.digikey.com/en/products/detail/te-connectivity-a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 | https://www.te.com/usa-en/product-1825967-1.datasheet.pdf | Switch\Tactile\SPST-NO\0.05A\24V\Through Hole
20 | S2 | 1 | SINGLE STEP | Homebrew-CPU-PCB:SW_1825967-1 | Digikey\450-1654-ND | https://www.digikey.com/en/products/detail/te-connectivity-a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 | https://www.te.com/usa-en/product-1825967-1.datasheet.pdf | Switch\Tactile\SPST-NO\0.05A\24V\Through Hole
21 | SW1 | 1 | TL2230 | Homebrew-CPU-PCB:TL2230EEF140 | Digikey\EG6031-ND | https://www.digikey.com/en/products/detail/e-switch/TL2230EE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 | https://eswitch.wpengine.com/wp-content/uploads/2022/06/TL22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 | Switch\Pushbutton\DPDT\Through Hole
22 | U1, U3 | 2 | LM555 | Homebrew-CPU-PCB:DIP-8_W7.62mm_Socket | Digikey\LM555CNNS/NOPB-ND | https://www.digikey.com/en/products/detail/texas-instruments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 | https://www.ti.com/lit/ds/symlink/lm555.pdf | 555 Timer/Oscillator\100kHz\8-PDIP
23 | U2 | 1 | 74LS00 | Homebrew-CPU-PCB:DIP-14_W7.62mm_Socket | Digikey\296-1626-ND | https://www.digikey.com/en/products/detail/texas-instruments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 | https://www.ti.com/lit/ds/symlink/sn7400.pdf | NAND Gate IC 4 Channel 14-PDI
24 | U4, U5, U6, U7, U8 | 5 | 74LS163 | Homebrew-CPU-PCB:DIP-16_W7.62mm_Socket | Digikey\296-3661-5-ND | https://www.digikey.com/en/products/detail/texas-instruments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 | https://www.ti.com/lit/ds/symlink/sn74ls163a.pdf | Binary Counter\4 Bit\Positive Edge\16-PDIP
25 | U9, U10 | 2 | SST39SF040-70-4C-PHE | Homebrew-CPU-PCB:PDIP32_PH_SST_MCH | Digikey\SST39SF040-70-4C-PHE-ND | https://www.digikey.com/en/products/detail/microchip-technol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 | https://ww1.microchip.com/downloads/en/DeviceDoc/20005022C.pdf | FLASH Memory\4Mbit\70ns\32-PDIP
